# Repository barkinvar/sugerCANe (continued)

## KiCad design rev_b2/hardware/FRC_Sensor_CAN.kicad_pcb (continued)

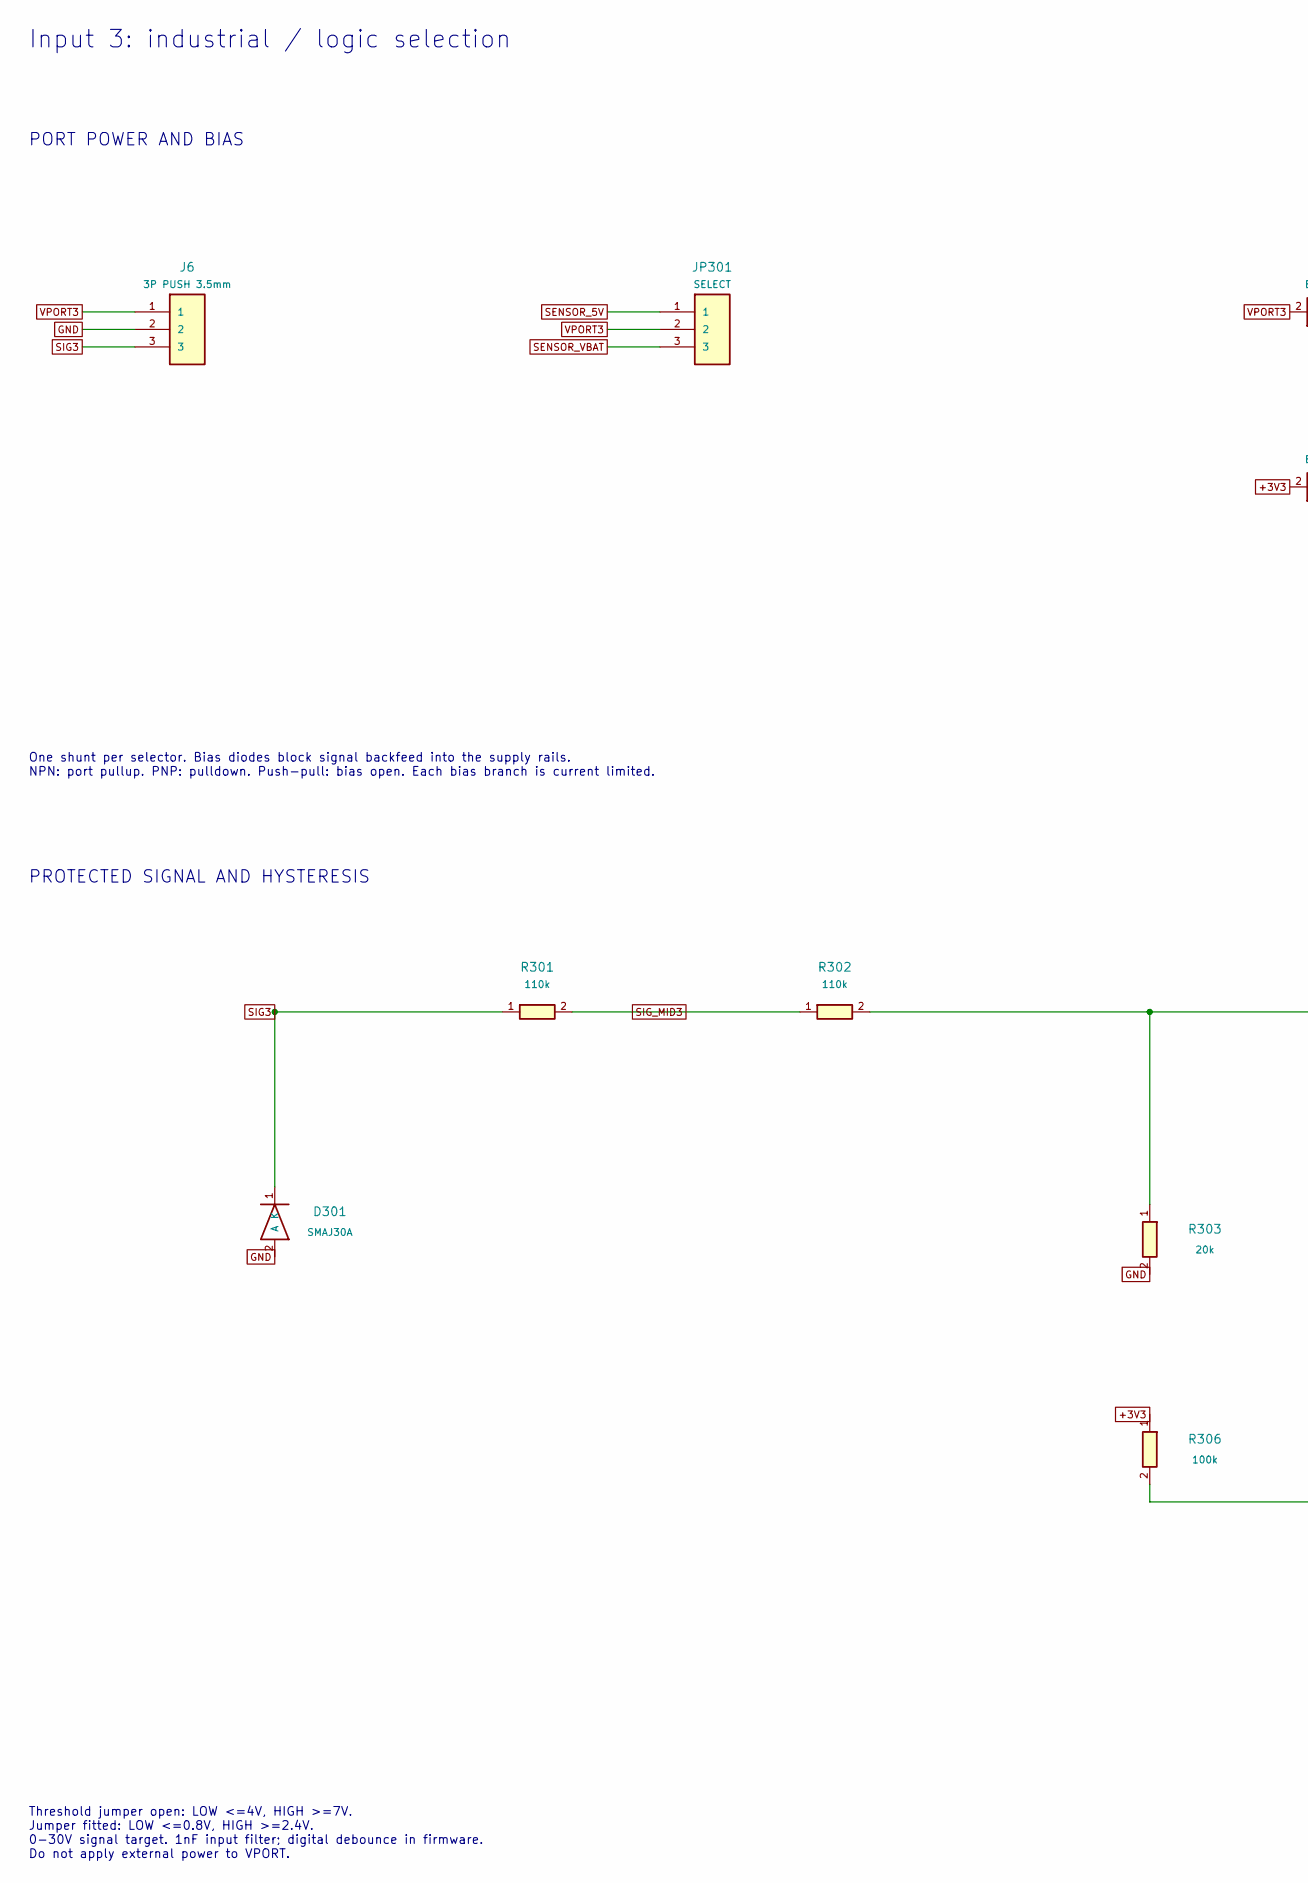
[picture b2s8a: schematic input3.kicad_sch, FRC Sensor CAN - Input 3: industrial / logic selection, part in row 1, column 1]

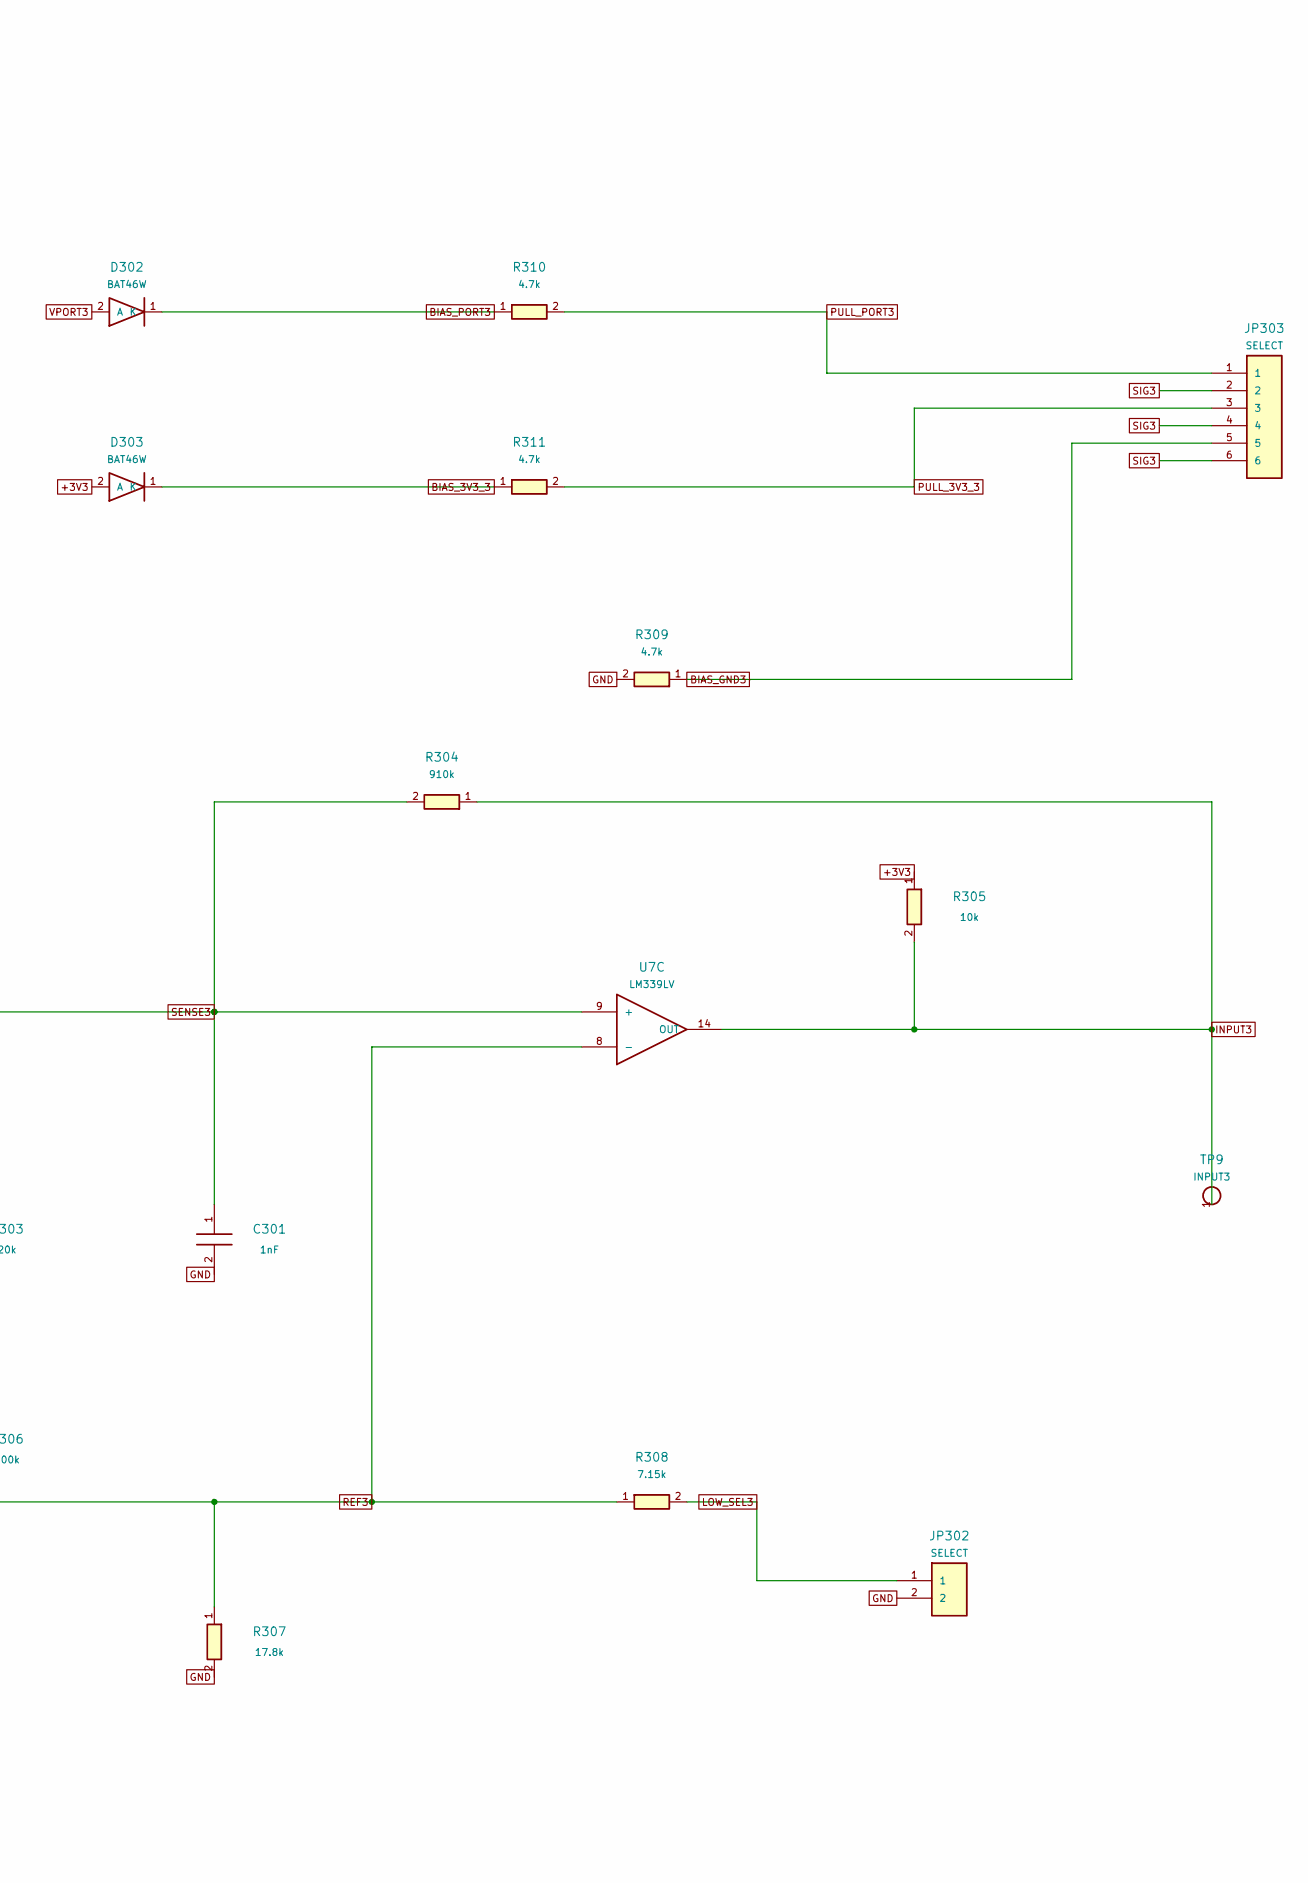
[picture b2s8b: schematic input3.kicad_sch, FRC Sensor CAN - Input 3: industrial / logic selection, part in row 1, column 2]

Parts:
C301: 1nF; C_0805_2012Metric; MPN CC0805JRNPO9BN102
D301: SMAJ30A; D_SMA; MPN SMAJ30A
D302, D303: BAT46W; D_SOD-123; MPN BAT46W-E3-18
J6: 3P PUSH 3.5mm; Weidmuller_LSF_90_3P; MPN 1824430000
JP301: SELECT; PinHeader_1x03_P2.00mm_Vertical; MPN M22-2010305
JP302: SELECT; PinHeader_1x02_P2.00mm_Vertical; MPN M22-2010205
JP303: SELECT; PinHeader_2x03_P2.00mm_Vertical; MPN M22-2020305
R301, R302: 110k; R_0805_2012Metric; MPN RC0805FR-07110KL
R303: 20k; R_0805_2012Metric; MPN RC0805FR-0720KL
R304: 910k; R_0805_2012Metric; MPN RC0805FR-07910KL
R305: 10k; R_0805_2012Metric; MPN 0805W8F1002T5E
R306: 100k; R_0805_2012Metric; MPN 0805W8F1003T5E
R307: 17.8k; R_0805_2012Metric; MPN ERJ-6ENF1782V
R308: 7.15k; R_0805_2012Metric; MPN RC0805FR-077K15L
R309: 4.7k; R_2010_5025Metric; MPN RC2010FK-074K7L
R310, R311: 4.7k; R_0805_2012Metric; MPN 0805W8F4701T5E
TP9: INPUT3; TestPoint_Pad_D2.0mm
U7: LM339LV; SOIC-14_3.9x8.7mm_P1.27mm; MPN LM339LVDR

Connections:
+3V3: D303.2 (A), R305.1, R306.1; also elsewhere on the board
BIAS_3V3_3: D303.1 (K), R311.1
BIAS_GND3: JP303.5, R309.1
BIAS_PORT3: D302.1 (K), R310.1
GND: C301.2, D301.2 (A), J6.2, JP302.2, R303.2, R307.2, R309.2; also elsewhere on the board
INPUT3: R304.1, R305.2, TP9.1, U7.14 (OUT); also elsewhere on the board
LOW_SEL3: JP302.1, R308.2
PULL_3V3_3: JP303.3, R311.2
PULL_PORT3: JP303.1, R310.2
REF3: R306.2, R307.1, R308.1, U7.8 (-)
SENSE3: C301.1, R302.2, R303.1, R304.2, U7.9 (+)
SENSOR_5V: JP301.1; also elsewhere on the board
SENSOR_VBAT: JP301.3; also elsewhere on the board
SIG3: D301.1 (K), J6.3, JP303.2, JP303.4, JP303.6, R301.1
SIG_MID3: R301.2, R302.1
VPORT3: D302.2 (A), J6.1, JP301.2

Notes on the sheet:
Input 3: industrial / logic selection
PORT POWER AND BIAS
One shunt per selector. Bias diodes block signal backfeed into the supply rails. NPN: port pullup. PNP: pulldown. Push-pull: bias open. Each bias branch is current limited.
PROTECTED SIGNAL AND HYSTERESIS
Threshold jumper open: LOW <=4V, HIGH >=7V. Jumper fitted: LOW <=0.8V, HIGH >=2.4V. 0-30V signal target. 1nF input filter; digital debounce in firmware. Do not apply external power to VPORT.

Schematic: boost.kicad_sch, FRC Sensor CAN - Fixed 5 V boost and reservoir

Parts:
C15, C16: 22uF; C_1206_3216Metric; MPN CL31A226KAHNNNE
C17: 100nF; C_0805_2012Metric; MPN CL21B104KCFNNNE
D4: SS14; D_SMA; MPN SS14-E3/61T
L2: 4.7uH; Bourns_SRP4020TA; MPN SRP4020TA-4R7M
U8: TPS613222A; SOT-23-5; MPN TPS613222ADBVR

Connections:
BOOST_SW: D4.2 (A), L2.2, U8.1 (SW)
GND: C15.2, C16.2, C17.2, U8.2 (GND); also elsewhere on the board
V4P2: L2.1; also elsewhere on the board
V5_INTERNAL: C15.1, C16.1, C17.1, D4.1 (K), U8.4 (VOUT); also elsewhere on the board

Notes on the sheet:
Fixed 5 V boost and reservoir
4.0 V INTERMEDIATE TO FIXED 5 V
TPS613222A: pins 1 SW, 2 GND, 4 OUT; pins 3/5 NC. D4 external Schottky shares rectifier current. C15/C16: two 22 uF 25 V ceramics. Target: 300 mA usable sensor load plus board logic. Qualify startup, ripple, thermal rise and cascaded-loop interaction at 5/12/22 V.

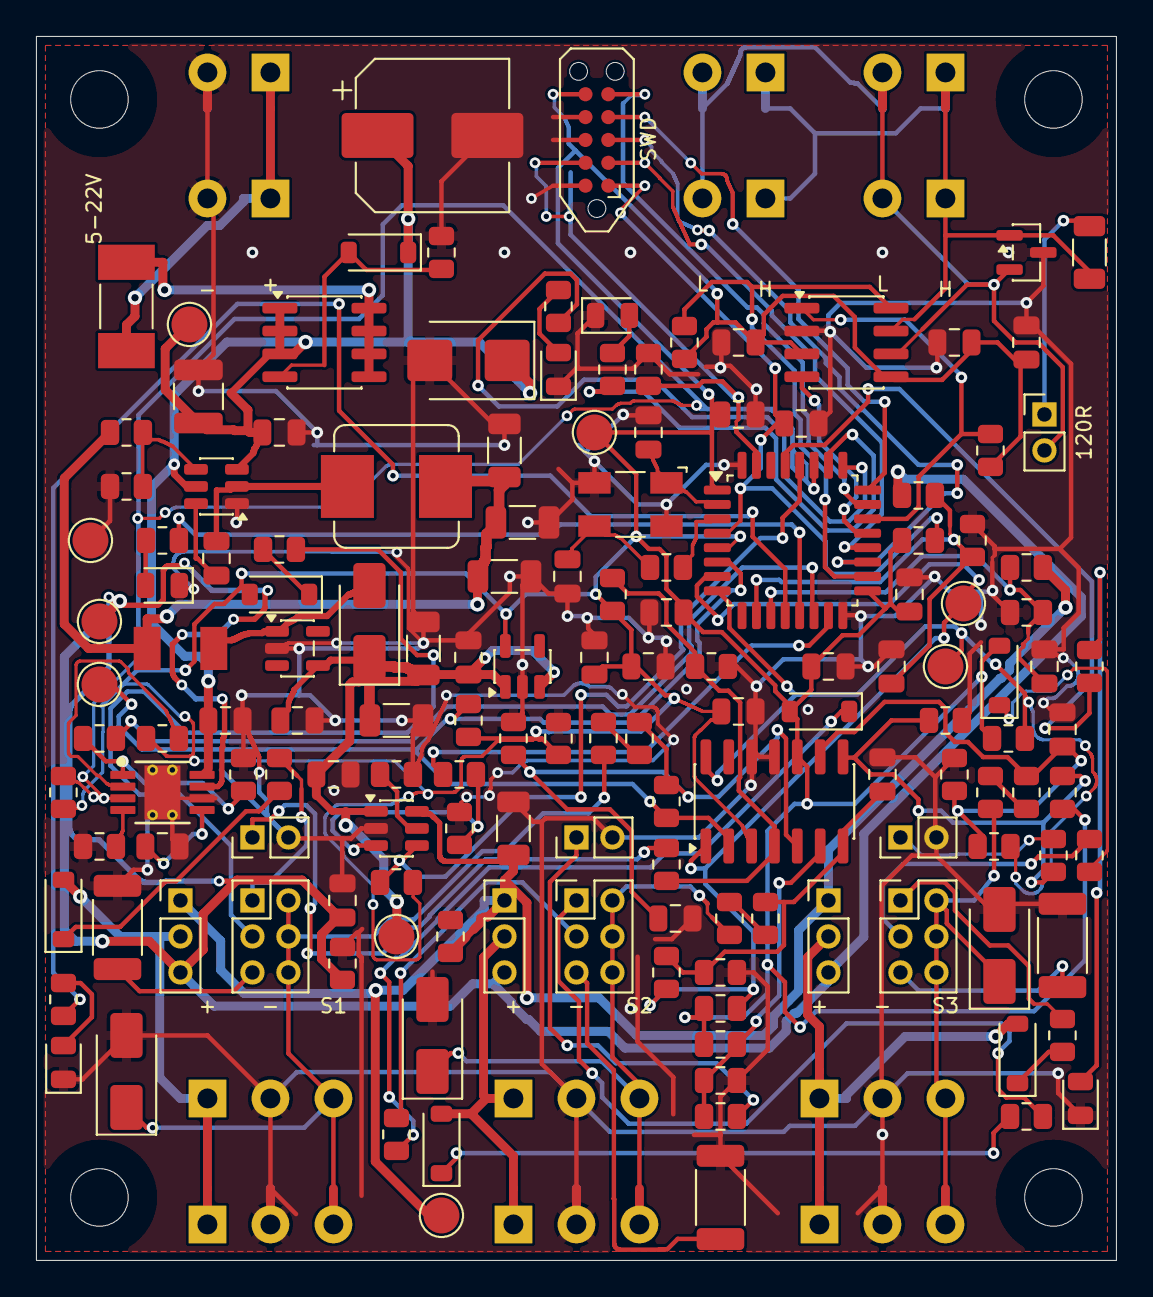
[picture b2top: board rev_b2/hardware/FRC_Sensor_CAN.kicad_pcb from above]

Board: 2 copper layers, 60.0 x 68.0 mm, 158 parts (0 on the bottom side), 87 nets.

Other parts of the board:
H1, H2, H3, H4: M3 NPTH

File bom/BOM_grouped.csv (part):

references,quantity,value,footprint,voltage,rated_power_W,temperature_coefficient_ppm_C,tolerance,dielectric,mpn,manufacturer,digikey_sku,digikey_url,reported_stock,unit_price_usd_qty1,unit_price_usd_qty10,checked_date,availability_note,alternative_mpn,evidence_kind,extended_usd_at_qty1_price,recommended_order_quantity
F1,1,1.5A FAST,FRC_Sensor_CAN:Fuse_Littelfuse-NANO2-451_453,,,,,,045101.5MRL,Littelfuse,F2579CT-ND,https://www.digikey.com/en/products/detail/littelfuse-inc/04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,7870,2.47,,2026-09-07,1.5A fast NANO2 fuse; upstream fused distribution still required.,,DigiKey catalog observation; stock/price must be reconfirmed before order,2.47,1
J1 J2 J3,3,2P 5.00mm,FRC_Sensor_CAN:Wuerth_691137710002,,,,,,691137710002,Wurth Elektronik,732-10955-ND,https://www.digikey.com/en/products/detail/w%C3%BCrth-elektr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,46145,0.41,,2026-09-07,Exact 5.00mm pitch; do not silently replace with5.08mm.,,DigiKey catalog observation; stock/price must be reconfirmed before order,1.23,3
J4 J5 J6 J7,4,3P 5.00mm,FRC_Sensor_CAN:Wuerth_691137710003,,,,,,691137710003,Wurth Elektronik,732-10956-ND,https://www.digikey.com/en/products/detail/w%C3%BCrth-elektr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,5153,0.66,,2026-09-07,Exact 5.00mm pitch; do not silently replace with5.08mm.,,DigiKey catalog observation; stock/price must be reconfirmed before order,2.64,4
Y1,1,8MHz 18pF,FRC_Sensor_CAN:Abracon_ABM3B_5.0x3.2mm,,,,,,ABM3B-8.000MHZ-B2-T,Abracon,535-9720-1-ND,https://www.digikey.com/en/products/detail/abracon-llc/ABM3B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,70541,0.76,,2026-09-07,"18pF load, ESR<=200ohm, 20ppm initial/50ppm stability, -20..70C.",,DigiKey catalog observation; stock/price must be reconfirmed before order,0.76,1
Q1,1,AO4485,FRC_Sensor_CAN:SOIC-8_3.9x4.9mm_P1.27mm,,,,,,AO4485,Alpha & Omega Semiconductor,785-1551-1-ND,https://www.digikey.com/en/products/detail/alpha-omega-semic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,64905,1.51,0.95,2026-09-07,"40V P-channel,SOIC8,20mohm max at-4.5V gate. Datasheet pin mapping checked.","DMP4025LSS-13; FDS4685 (same pin arrangement; recheck Rds,SOA and stock)",DigiKey catalog observation; stock/price must be reconfirmed before order,1.51,1
U2,1,AP2112K-3.3,FRC_Sensor_CAN:SOT-23-5,,,,,,AP2112K-3.3TRG1,Diodes Incorporated,AP2112K-3.3TRG1DICT-ND,https://www.digikey.com/en/products/detail/diodes-incorporat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,159040,0.28,,2026-09-07,,,DigiKey catalog observation; stock/price must be reconfirmed before order,0.28,1
D102 D103 D202 D203 D302 D303 D402 D403,8,BAT46W,FRC_Sensor_CAN:D_SOD-123,,,,,,BAT46W-E3-18,Vishay,BAT46W-E3-18GICT-ND,https://www.digikey.com/en/products/detail/vishay-general-se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,19931,0.52,,2026-09-07,"100V reverse blocking, SOD123. Catalog showed$0.49-$0.52 by packaging; conservative price used. Do not substitute30V BAT54.",,DigiKey catalog observation; stock/price must be reconfirmed before order,4.16,10
C25 C26,2,30pF,FRC_Sensor_CAN:C_0805_2012Metric,50V,,,5%,C0G,C0805C300J5GACTU,KEMET,399-C0805C300J5GACTUCT-ND,https://www.digikey.com/en/products/detail/kemet/C0805C300J5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,9211,0.33,,2026-09-07,"30pF,50V,C0G,5%,0805.",,DigiKey catalog observation; stock/price must be reconfirmed before order,0.66,4
C101 C201 C301 C401,4,1nF,FRC_Sensor_CAN:C_0805_2012Metric,50V,,,5%,C0G,CC0805JRNPO9BN102,YAGEO,311-1122-1-ND,https://www.digikey.com/en/products/detail/yageo/CC0805JRNPO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,105431,0.15,,2026-09-07,"1nF,50V,C0G,5%,0805.",,DigiKey catalog observation; stock/price must be reconfirmed before order,0.6,6
C10 C23 C42 C7,4,1uF,FRC_Sensor_CAN:C_0805_2012Metric,50V,,,10%,X7R,CC0805KKX7R9BB105,YAGEO,311-1886-1-ND,https://www.digikey.com/en/products/detail/yageo/CC0805KKX7R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,112870,0.32,,2026-09-07,"1uF,50V,X7R,10%,0805. Lower-cost stocked selection.",C0805C105K5RACTU (KEMET),DigiKey catalog observation; stock/price must be reconfirmed before order,1.28,6
C28 C29,2,10nF,FRC_Sensor_CAN:C_0805_2012Metric,50V,,,10%,X7R,CC0805KRX7R9BB103,YAGEO,311-1136-1-ND,https://www.digikey.com/en/products/detail/yageo/CC0805KRX7R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,360198,0.11,,2026-09-07,"10nF,50V,X7R,0805; stock from DigiKey substitute table.",C0805C103K5RACTU,DigiKey catalog observation; stock/price must be reconfirmed before order,0.22,4
C11 C20 C21 C22 C27 C3 C40 C41 C50 C6 C9,11,100nF,FRC_Sensor_CAN:C_0805_2012Metric,50V,,,10%,X7R,CC0805KRX7R9BB104,YAGEO,311-1140-1-ND,https://www.digikey.com/en/products/detail/yageo/CC0805KRX7R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,1921549,0.11,,2026-09-07,"100nF,50V,X7R,0805; stock from DigiKey substitute table.",C0805C104K5RACTU,DigiKey catalog observation; stock/price must be reconfirmed before order,1.21,14
C14,1,33nF,FRC_Sensor_CAN:C_0805_2012Metric,50V,,,10%,X7R,CC0805KRX7R9BB333,YAGEO,311-1374-1-ND,https://www.digikey.com/en/products/detail/yageo/CC0805KRX7R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,24641,0.14,0.078,2026-09-07,"33nF,50V,X7R,10%,0805; battery switch latch timing. Direct US product listing checked2026-09-07.",C0805C333K5RACTU; CC0805KPX7R9BB333 (verify package and timing tolerance),DigiKey catalog observation; stock/price must be reconfirmed before order,0.14,3
C12 C13 C4 C5,4,22uF,FRC_Sensor_CAN:C_1206_3216Metric,25V,,,10%,X5R,CL31A226KAHNNNE,Samsung Electro-Mechanics,1276-3047-1-ND,https://www.digikey.com/en/products/detail/samsung-electro-m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,426249,0.48,,2026-09-07,22uF25VX5R1206. Manufacturer typical capacitance change is about-39% near5.18V; three parallel capacitors used on buck output.,TMK316BBJ226ML-T (20% tolerance requires capacitance recheck),DigiKey catalog observation; stock/price must be reconfirmed before order,1.92,6
C2,1,10uF,FRC_Sensor_CAN:C_1210_3225Metric,50V,,,10%,X7R,CL32B106KBJNNWE,Samsung Electro-Mechanics,1276-3388-1-ND,https://www.digikey.com/en/products/detail/samsung-electro-m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,149003,0.62,,2026-09-07,"10uF,50V,X7R,1210; DigiKey US Spanish-language catalog observation.",,DigiKey catalog observation; stock/price must be reconfirmed before order,0.62,3
C1,1,47uF,FRC_Sensor_CAN:CP_Elec_6.3x5.8,35V,,,20%,,EEE-FK1V470P,Panasonic Industry,PCE3842CT-ND,https://www.digikey.com/en/products/detail/panasonic-industr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,1183,0.55,,2026-09-07,"47uF35V,6.3mm diameter,6.1mm max mounted height,240mA ripple at100kHz.",,DigiKey catalog observation; stock/price must be reconfirmed before order,0.55,3
R107 R207 R307 R407,4,17.8k,FRC_Sensor_CAN:R_0805_2012Metric,,0.125,100,1%,,ERJ-6ENF1782V,Panasonic Industry,P17.8KCCT-ND,https://www.digikey.com/en/products/detail/panasonic-industr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,33381,0.12,,2026-09-07,,RC0805FR-0717K8L; CRCW080517K8FKTA,DigiKey catalog observation; stock/price must be reconfirmed before order,0.48,6
D20,1,ESD2CAN24-Q1,FRC_Sensor_CAN:SOT-23,,,,,,ESD2CAN24DBZRQ1,Texas Instruments,296-ESD2CAN24DBZRQ1CT-ND,https://www.digikey.com/en/products/detail/texas-instruments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,255809,0.87,,2026-09-07,,,DigiKey catalog observation; stock/price must be reconfirmed before order,0.87,1
U7,1,LM2901BIDR,FRC_Sensor_CAN:SOIC-14_3.9x8.7mm_P1.27mm,,,,,,LM2901BIDR,Texas Instruments,296-LM2901BIDRCT-ND,https://www.digikey.com/en/products/detail/texas-instruments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,3349,0.29,,2026-09-07,B-grade comparator required; older LM2901 variants have different error bounds.,,DigiKey catalog observation; stock/price must be reconfirmed before order,0.29,1
U1,1,LMR51420XDDCR,FRC_Sensor_CAN:TSOT-23-6,,,,,,LMR51420XDDCR,Texas Instruments,296-LMR51420XDDCRCT-ND,https://www.digikey.com/en/products/detail/texas-instruments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,14239,1.32,,2026-09-07,,,DigiKey catalog observation; stock/price must be reconfirmed before order,1.32,1
D10 D12 D13 D14 D15,5,GREEN,FRC_Sensor_CAN:LED_0805_2012Metric,,,,,,LTST-C170KGKT,Lite-On,160-1414-1-ND,https://www.digikey.com/en/products/detail/lite-on-inc/LTST-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,498450,0.19,,2026-09-07,"Green0805,typical Vf2V. Board current approximately1.3mA.",,DigiKey catalog observation; stock/price must be reconfirmed before order,0.95,7
D11,1,RED,FRC_Sensor_CAN:LED_0805_2012Metric,,,,,,LTST-C170KRKT,Lite-On,160-1415-1-ND,https://www.digikey.com/en/products/detail/lite-on-inc/LTST-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,489805,0.18,,2026-09-07,"Red0805,typical Vf2V. Board current approximately1.3mA.",,DigiKey catalog observation; stock/price must be reconfirmed before order,0.18,3
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
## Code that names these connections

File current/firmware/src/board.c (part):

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    GPIOA->BSRR = (1u << 8) | (1u << (15+16)); /* Transceiver standby before GPIO output enable. */
    GPIOB->BSRR = (1u << (3+16)) | (1u << (7+16));
    for (unsigned i=0;i<5;i++) gpio_mode(GPIOA,i,0);
    /* PA3: TPS259620 fault; PA4: TPS2553 active-low fault. Both open drain. */
    GPIOA->PUPDR = (GPIOA->PUPDR & ~((3u<<6)|(3u<<8))) | (1u<<6) | (1u<<8);
    GPIOA->BSRR=7u<<5; /* PMOS gates HIGH = off before output enable. */
    for (unsigned i=5;i<=7;i++) gpio_mode(GPIOA,i,1);
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    gpio_mode(GPIOB,3,1); /* Single status LED. */
    GPIOB->BSRR=((1u<<5)|(1u<<6)|(1u<<4))<<16;
    gpio_mode(GPIOB,5,1);gpio_mode(GPIOB,6,1);gpio_mode(GPIOB,4,1);
    gpio_mode(GPIOB,7,1); /* HIGH enables 12 V; PB0/PB1 remain analog. */
    /* PA13/14 retain SWD; HSE, UART and CAN are configured by their drivers. */
}
void board_voltage_guard_init(void) {
    RCC->APB1ENR |= RCC_APB1ENR_PWREN;
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    for (;;) {
    }
}
/* PB3 AF2 = TIM2_CH2. TIM2 update requests use DMA1 channel 2 (RM0091
 * table 29). PWM preload gives DMA a whole bit period to prepare the next
 * duty cycle. No interrupt masking, polling loop or ISR is needed. */
static uint16_t led_duty[26];
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    return ok && sc_config_valid((const sc_config_record *)address);
}

/* Rev G: PA15 enables U4, PB7 drives the active-HIGH Q3 enable transistor. */
void board_power_set(uint8_t enabled) {
    GPIOA->BSRR=(enabled&2u)?(1u<<15):(1u<<(15+16));
    GPIOB->BSRR=(enabled&1u)?(1u<<7):(1u<<(7+16));
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
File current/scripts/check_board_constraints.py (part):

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 for ref in (f'Q{ch}01',f'Q{ch}02'):
  assert math.dist(p.ToMM(fps[ref].GetPosition()),CONTRACT['placements'][ref]['at_mm'])<1e-6
assert all(not d.IsOnLayer(p.F_Paste) for d in pads('JP2').values())
service=pads('J8');mapping={'1':'NRST','2':'UART_RX','3':'UART_TX','4':'SWCLK','5':'SWDIO','6':'+3V3','7':'GND','8':'GND','9':'BOOT0','10':'GND'}
assert nets('J8')==mapping
assert parts['J8']['mpn']=='PM254V-12-10P-H85'
assert fps['J8'].GetValue()=='2x5 SERVICE SOCKET 2.54mm'
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report['status_routes']={net:dict(track_length_mm=sum(p.ToMM(t.GetLength()) for t in tracks[net]),vias=vias[net],layers=sorted({b.GetLayerName(t.GetLayer()) for t in tracks[net]})) for net in ('STATUS_5V_DATA','STATUS_DIN')}
led_bypass={}
for ref,ic,pin,limit in [('C74','U10','5',3),('C75','D10','2',4)]:
 length=local_path('V5_INTERNAL',pads(ref)['1'],pads(ic)[pin])
 assert length<limit,(ref,length)
 led_bypass[ref]=dict(supply_top_path_mm=length)
report['rgb_local_bypass']=led_bypass
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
